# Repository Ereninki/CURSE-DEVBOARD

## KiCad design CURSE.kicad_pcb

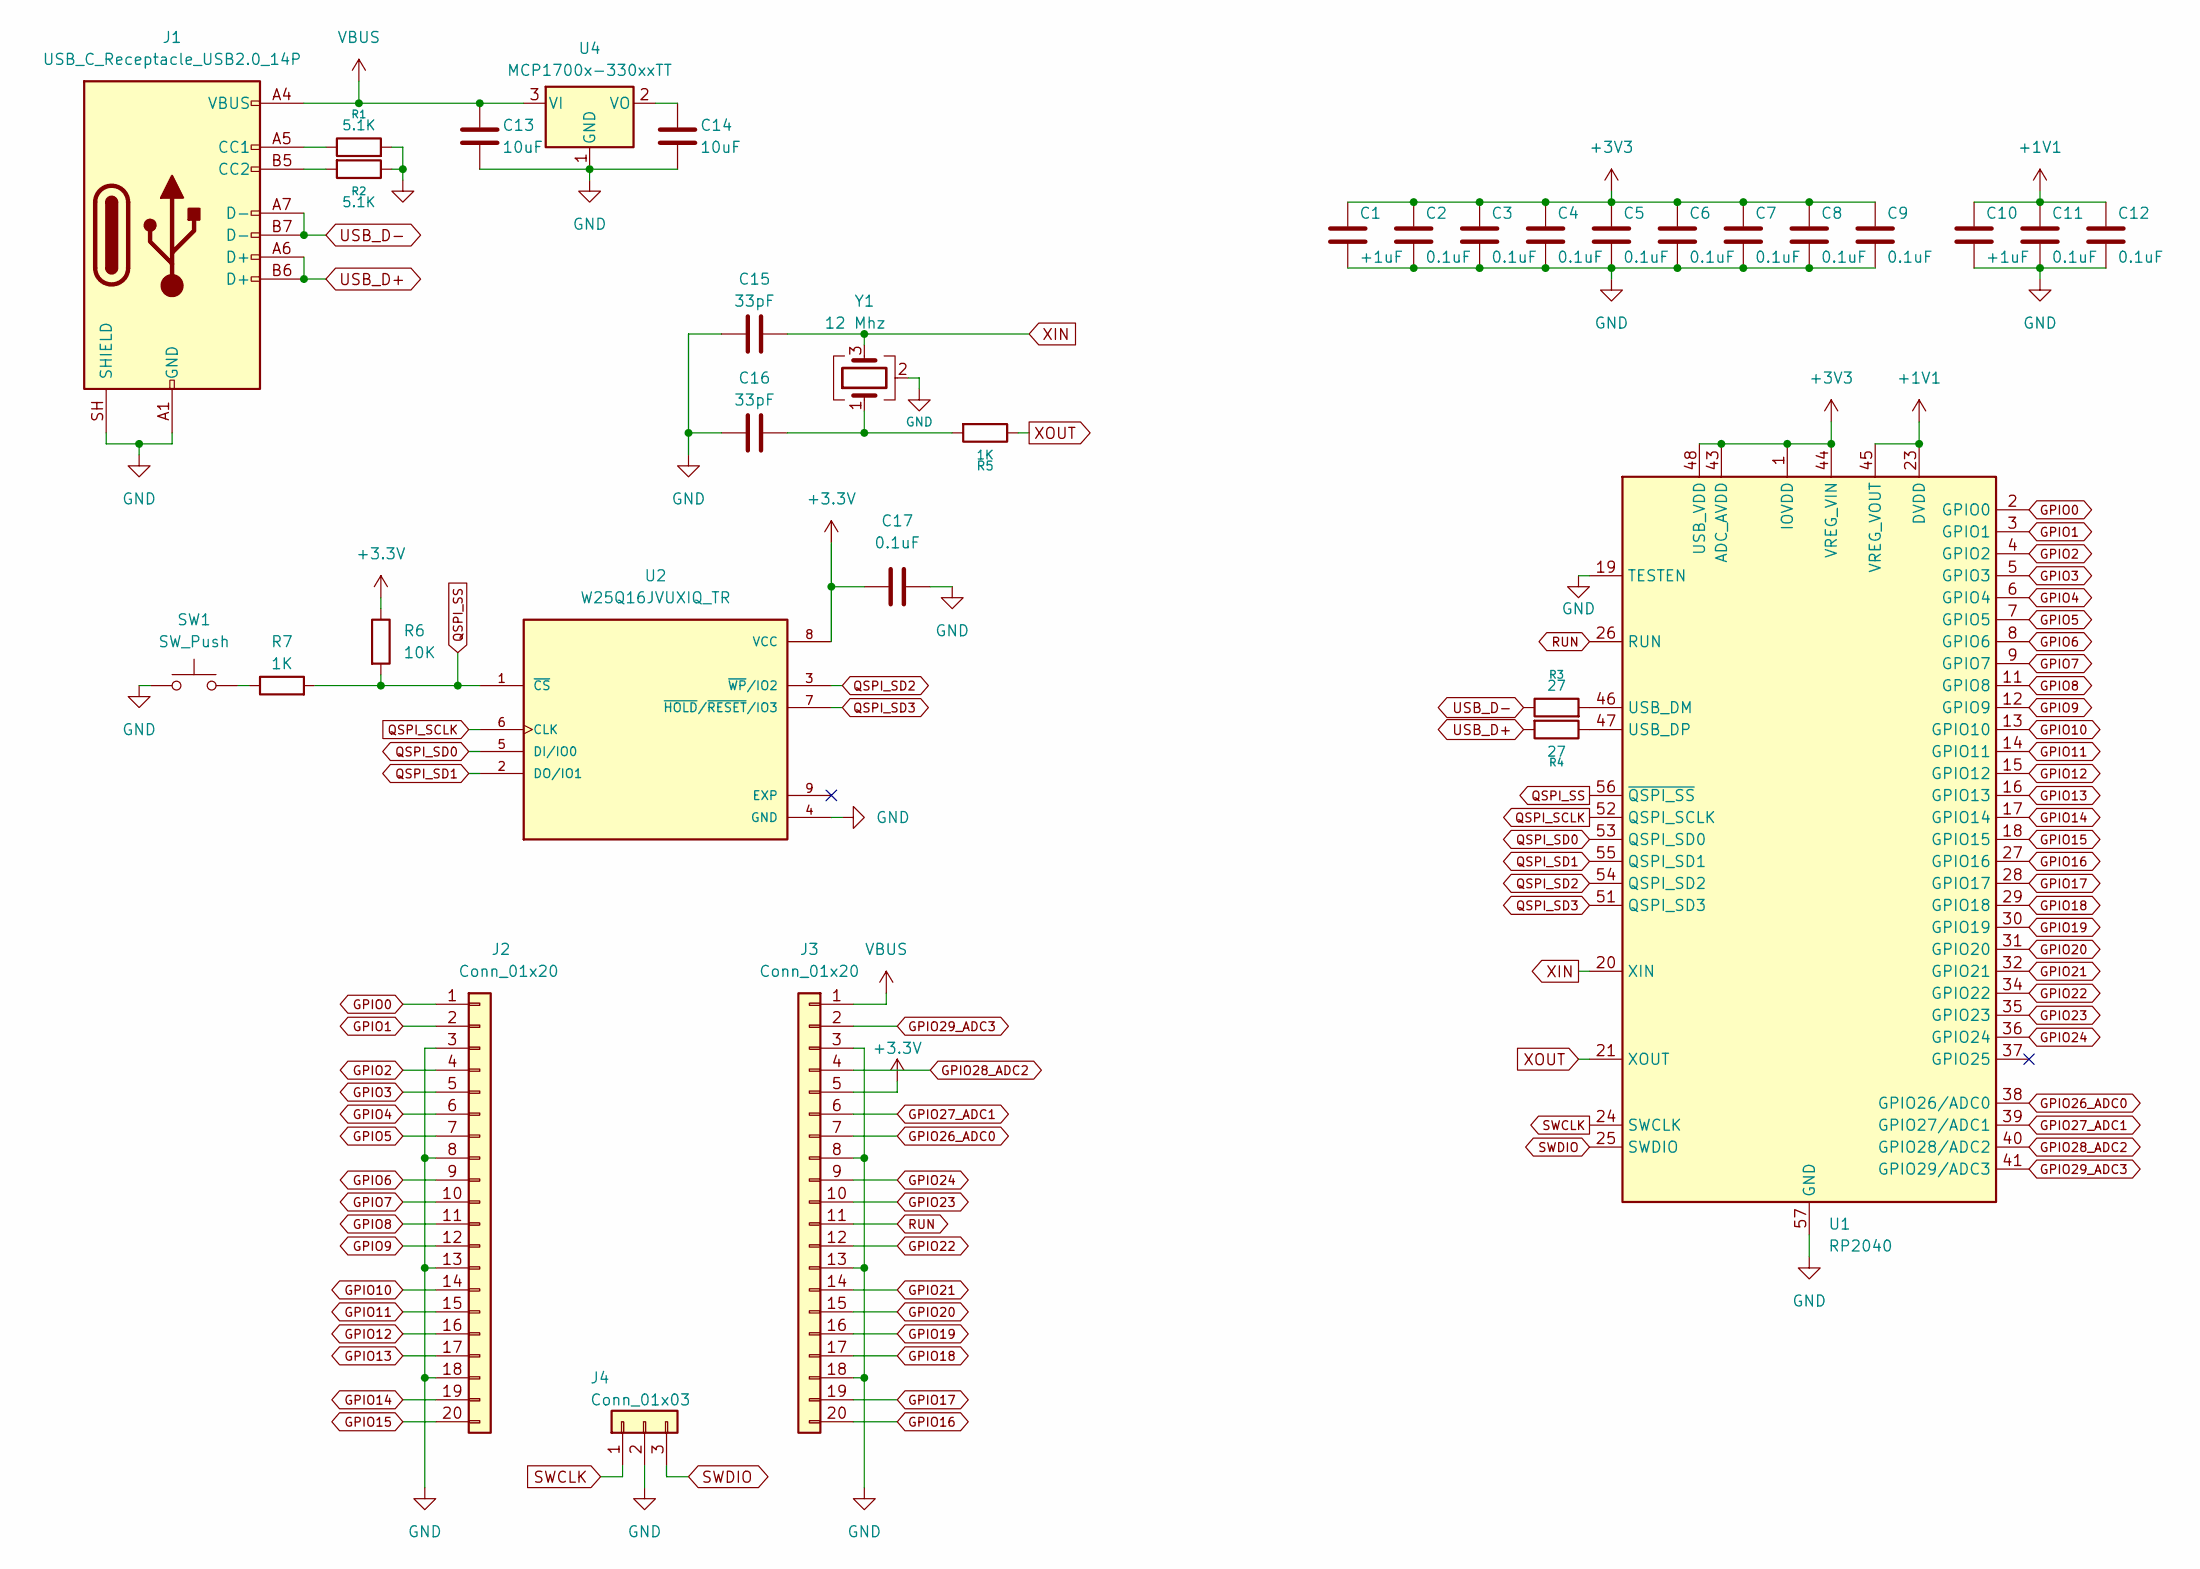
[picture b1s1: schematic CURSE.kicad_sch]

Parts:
C1, C10: +1uF; C_0402_1005Metric
C2, C3, C4, C5, C6, C7, C8, C9, C11, C12, C17: 0.1uF; C_0402_1005Metric
C13, C14: 10uF; C_0603_1608Metric
C15, C16: 33pF; C_0402_1005Metric
J1: USB_C_Receptacle_USB2.0_14P; USB_C_Receptacle_HRO_TYPE-C-31-M-12
J2, J3: Conn_01x20; PinHeader_1x20_P2.54mm_Vertical
J4: Conn_01x03; PinHeader_1x03_P2.54mm_Vertical
R1, R2: 5.1K; R_0402_1005Metric
R3, R4: 27; R_0402_1005Metric
R5, R7: 1K; R_0402_1005Metric
R6: 10K; R_0402_1005Metric
SW1: SW_Push; SW_Push_SPST_NO_Alps_SKRK
U1: RP2040; QFN-56-1EP_7x7mm_P0.4mm_EP3.2x3.2mm
U2: W25Q16JVUXIQ_TR; Winbond_USON-8-1EP_3x2mm_P0.5mm_EP0.2x1.6mm; PARTREV H
U4: MCP1700x-330xxTT; SOT-23
Y1: 12 Mhz; Crystal_SMD_3225-4Pin_3.2x2.5mm

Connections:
+1V1: C10.1, C11.1, C12.1, U1.23 (DVDD), U1.45 (VREG_VOUT), U1.50 (DVDD)
+3.3V: C17.1, J3.5, R6.1, U2.8 (VCC); also elsewhere on the board
+3V3: C1.1, C2.1, C3.1, C4.1, C5.1, C6.1, C7.1, C8.1, C9.1, U1.1 (IOVDD), U1.10 (IOVDD), U1.22 (IOVDD), U1.33 (IOVDD), U1.42 (IOVDD), U1.43 (ADC_AVDD), U1.44 (VREG_VIN), U1.48 (USB_VDD), U1.49 (IOVDD)
GND: C1.2, C2.2, C3.2, C4.2, C5.2, C6.2, C7.2, C8.2, C9.2, C10.2, C11.2, C12.2, C13.2, C14.2, C15.1, C16.1, C17.2, J1.A1 (GND), J1.A12 (GND), J1.B1 (GND), J1.B12 (GND), J1.SH (SHIELD), J2.3, J2.8, J2.13, J2.18, J3.3, J3.8, J3.13, J3.18, J4.2, R1.2, R2.1, SW1.1, U1.19 (TESTEN), U1.57 (GND), U2.4 (GND), U4.1 (GND), Y1.2 (G), Y1.4 (G); also elsewhere on the board
GPIO0: J2.1, U1.2 (GPIO0)
GPIO1: J2.2, U1.3 (GPIO1)
GPIO2: J2.4, U1.4 (GPIO2)
GPIO3: J2.5, U1.5 (GPIO3)
GPIO4: J2.6, U1.6 (GPIO4)
GPIO5: J2.7, U1.7 (GPIO5)
GPIO6: J2.9, U1.8 (GPIO6)
GPIO7: J2.10, U1.9 (GPIO7)
GPIO8: J2.11, U1.11 (GPIO8)
GPIO9: J2.12, U1.12 (GPIO9)
GPIO10: J2.14, U1.13 (GPIO10)
GPIO11: J2.15, U1.14 (GPIO11)
GPIO12: J2.16, U1.15 (GPIO12)
GPIO13: J2.17, U1.16 (GPIO13)
GPIO14: J2.19, U1.17 (GPIO14)
GPIO15: J2.20, U1.18 (GPIO15)
GPIO16: J3.20, U1.27 (GPIO16)
GPIO17: J3.19, U1.28 (GPIO17)
GPIO18: J3.17, U1.29 (GPIO18)
GPIO19: J3.16, U1.30 (GPIO19)
GPIO20: J3.15, U1.31 (GPIO20)
GPIO21: J3.14, U1.32 (GPIO21)
GPIO22: J3.12, U1.34 (GPIO22)
GPIO23: J3.10, U1.35 (GPIO23)
GPIO24: J3.9, U1.36 (GPIO24)
GPIO26_ADC0: J3.7, U1.38 (GPIO26/ADC0)
GPIO27_ADC1: J3.6, U1.39 (GPIO27/ADC1)
GPIO28_ADC2: J3.4, U1.40 (GPIO28/ADC2)
GPIO29_ADC3: J3.2, U1.41 (GPIO29/ADC3)
unnamed: C16.2, R5.2, Y1.1
unnamed: J1.A5 (CC1), R1.1
unnamed: J1.B5 (CC2), R2.2
unnamed: R7.1, SW1.2
unnamed: R3.2, U1.46 (USB_DM)
unnamed: R4.1, U1.47 (USB_DP)
unnamed: C14.1, U4.2 (VO)
QSPI_SCLK: U1.52 (QSPI_SCLK), U2.6 (CLK)
QSPI_SD0: U1.53 (QSPI_SD0), U2.5 (DI/IO0)
QSPI_SD1: U1.55 (QSPI_SD1), U2.2 (DO/IO1)
QSPI_SD2: U1.54 (QSPI_SD2), U2.3 (~WP/IO2)
QSPI_SD3: U1.51 (QSPI_SD3), U2.7 (~HOLD/~RESET/IO3)
QSPI_SS: R6.2, R7.2, U1.56 (~QSPI_SS), U2.1 (~CS)
RUN: J3.11, U1.26 (RUN)
SWCLK: J4.1, U1.24 (SWCLK)
SWDIO: J4.3, U1.25 (SWDIO)
USB_D+: J1.A6 (D+), J1.B6 (D+), R4.2
USB_D-: J1.A7 (D-), J1.B7 (D-), R3.1
VBUS: C13.1, J1.A4 (VBUS), J1.A9 (VBUS), J1.B4 (VBUS), J1.B9 (VBUS), J3.1, U4.3 (VI)
XIN: C15.2, U1.20 (XIN), Y1.3
XOUT: R5.1, U1.21 (XOUT)

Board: 2 copper layers, 34 parts (0 on the bottom side), 54 nets, no tracks yet.

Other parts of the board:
C17#2: 0.1uF; C_0402_1005Metric

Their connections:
+3.3V: C17#2.1; also elsewhere on the board
GND: C17#2.2; also elsewhere on the board
